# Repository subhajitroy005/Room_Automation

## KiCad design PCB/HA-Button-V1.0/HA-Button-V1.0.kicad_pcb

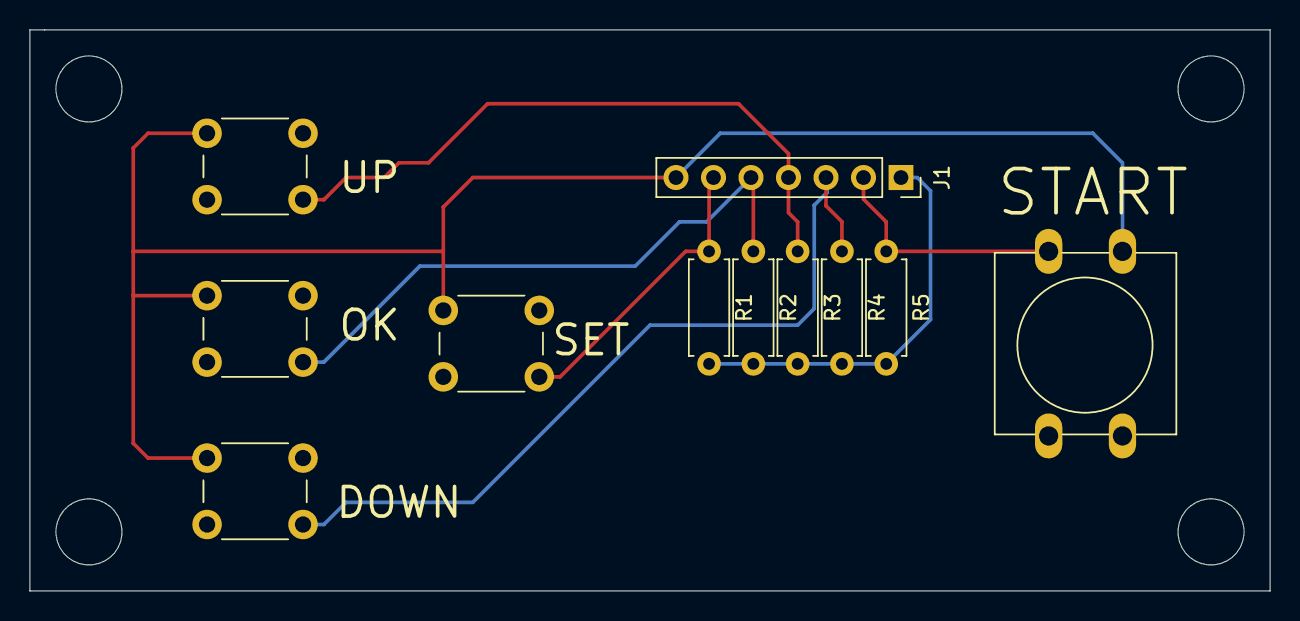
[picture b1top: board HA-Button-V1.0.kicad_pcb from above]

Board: 2 copper layers, 84.0 x 38.0 mm, 11 parts (0 on the bottom side), 7 nets.

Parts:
DOWN: DOWN; SW_PUSH_6mm
J1: MAIN_Board_Connecto; PinSocket_1x07_P2.54mm_Vertical
OK: OK; SW_PUSH_6mm
R1, R2, R3, R4: 1K; R_Axial_DIN0207_L6.3mm_D2.5mm_P7.62mm_Horizontal
R5: 1k; R_Axial_DIN0207_L6.3mm_D2.5mm_P7.62mm_Horizontal
SET: SETUP; SW_PUSH_6mm
START: Start; SW_PUSH-12mm
UP: UP; SW_PUSH_6mm

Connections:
5V-P: DOWN.1, J1.7, OK.1, SET.1, START.1, UP.1
DOWN_BTN: DOWN.2, J1.3, R4.1
GND: J1.1, R1.2, R2.2, R3.2, R4.2, R5.2
OK_BTN: J1.5, OK.2, R2.1
SET_BTN: J1.6, R1.1, SET.2
START_BTN: J1.2, R5.1, START.2
UP_BTN: J1.4, R3.1, UP.2

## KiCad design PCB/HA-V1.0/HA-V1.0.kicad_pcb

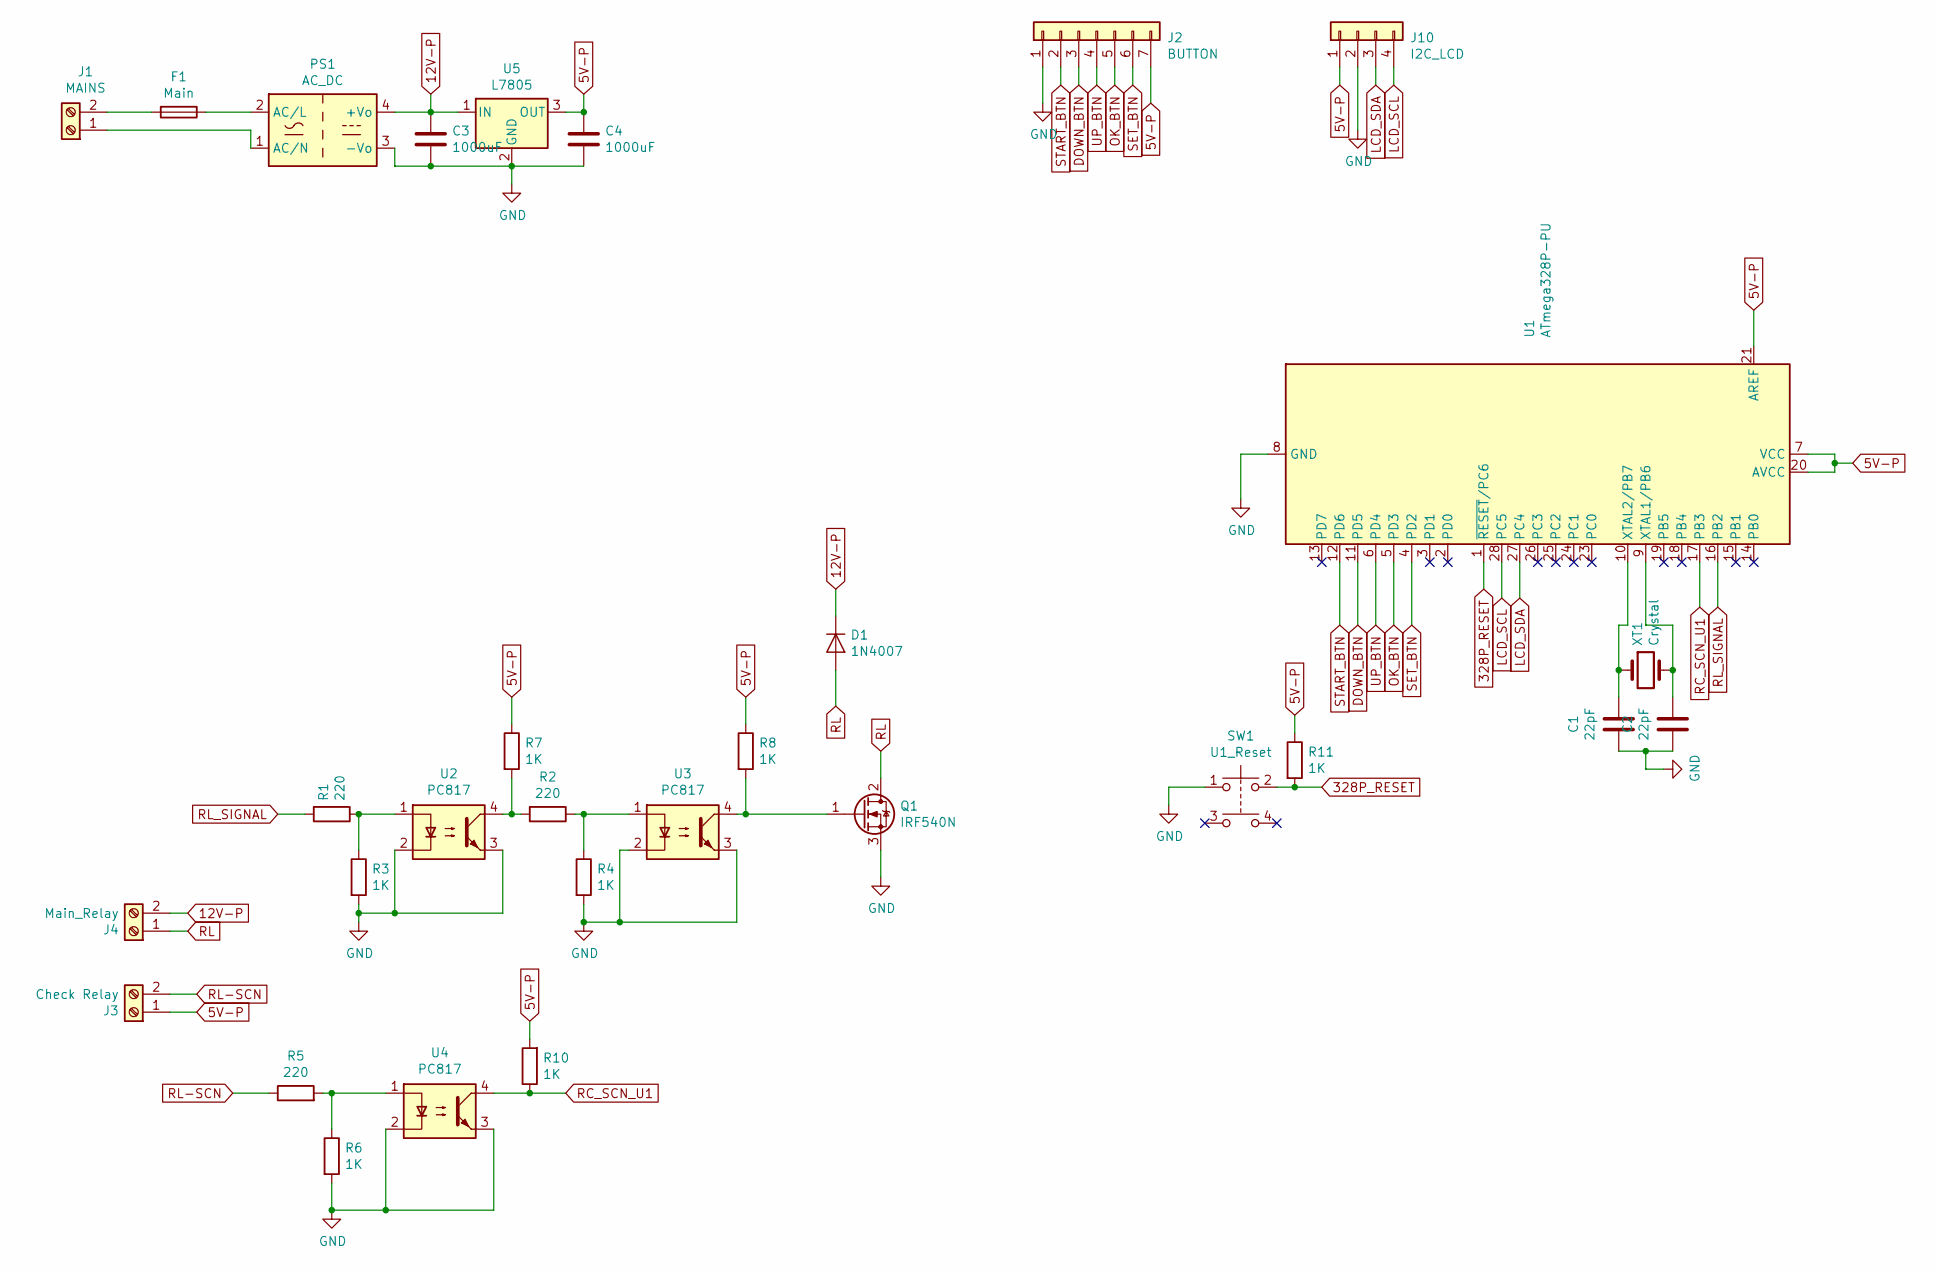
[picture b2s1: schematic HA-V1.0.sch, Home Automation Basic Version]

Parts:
C1, C2: 22pF; C_Disc_D3.0mm_W1.6mm_P2.50mm
C3, C4: 1000uF; C_Radial_D10.0mm_H16.0mm_P5.00mm
D1: 1N4007; D_DO-41_SOD81_P10.16mm_Horizontal
F1: Main; Fuse_SunFuse-6HP
J1: MAINS; PhoenixContact_MCV_1,5_2-G-5.08_1x02_P5.08mm_Vertical
J2: BUTTON; PinSocket_1x07_P2.54mm_Vertical
J3: Check Relay; TE_826576-2_1x02_P3.96mm_Vertical
J4: Main_Relay; TE_826576-2_1x02_P3.96mm_Vertical
J10: I2C_LCD; PinHeader_1x04_P2.54mm_Vertical; Digikey PN A101067-ND
PS1: AC_DC; Converter_ACDC_MeanWell_IRM-10-xx_THT
Q1: IRF540N; TO-220-3_Vertical
R1, R2, R5: 220; R_Axial_DIN0207_L6.3mm_D2.5mm_P7.62mm_Horizontal
R3, R4, R6, R7, R8, R10, R11: 1K; R_Axial_DIN0207_L6.3mm_D2.5mm_P7.62mm_Horizontal
SW1: U1_Reset; SW_PUSH_6mm_H4.3mm
U1: ATmega328P-PU; DIP-28_W7.62mm
U2, U3, U4: PC817; DIP-4_W7.62mm
U5: L7805; TO-220-3_Vertical
XT1: Crystal; Crystal_HC52-U_Vertical

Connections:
5V-P: C4.1, J2.7, J3.1, J10.1, R7.1, R8.1, R10.2, R11.1, U1.7 (VCC), U1.20 (AVCC), U1.21 (AREF), U5.3 (OUT); also elsewhere on the board
12V-P: C3.1, D1.1 (K), J4.2, PS1.4 (+Vo), U5.1 (IN); also elsewhere on the board
328P_RESET: R11.2, SW1.2, U1.1 (~RESET~/PC6)
DOWN_BTN: J2.3, U1.11 (PD5)
GND: C1.2, C2.2, C3.2, C4.2, J2.1, J10.2, PS1.3 (-Vo), Q1.3 (S), R3.2, R4.2, R6.2, SW1.1, U1.8 (GND), U1.22 (GND), U2.2, U2.3, U3.2, U3.3, U4.2, U4.3, U5.2 (GND)
LCD_SCL: J10.4, U1.28 (PC5)
LCD_SDA: J10.3, U1.27 (PC4)
unnamed: C1.1, U1.10 (XTAL2/PB7), XT1.1
unnamed: C2.1, U1.9 (XTAL1/PB6), XT1.2
unnamed: F1.1, PS1.2 (AC/L)
unnamed: F1.2, J1.2
unnamed: J1.1, PS1.1 (AC/N)
unnamed: Q1.1 (G), R8.2, U3.4
unnamed: R1.1, R3.1, U2.1
unnamed: R2.1, R4.1, U3.1
unnamed: R2.2, R7.2, U2.4
unnamed: R5.2, R6.1, U4.1
OK_BTN: J2.5, U1.5 (PD3)
RC_SCN_U1: R10.1, U1.17 (PB3), U4.4
RL: D1.2 (A), J4.1, Q1.2 (D); also elsewhere on the board
RL-SCN: J3.2, R5.1; also elsewhere on the board
RL_SIGNAL: R1.2, U1.16 (PB2)
SET_BTN: J2.6, U1.4 (PD2)
START_BTN: J2.2, U1.12 (PD6)
UP_BTN: J2.4, U1.6 (PD4)

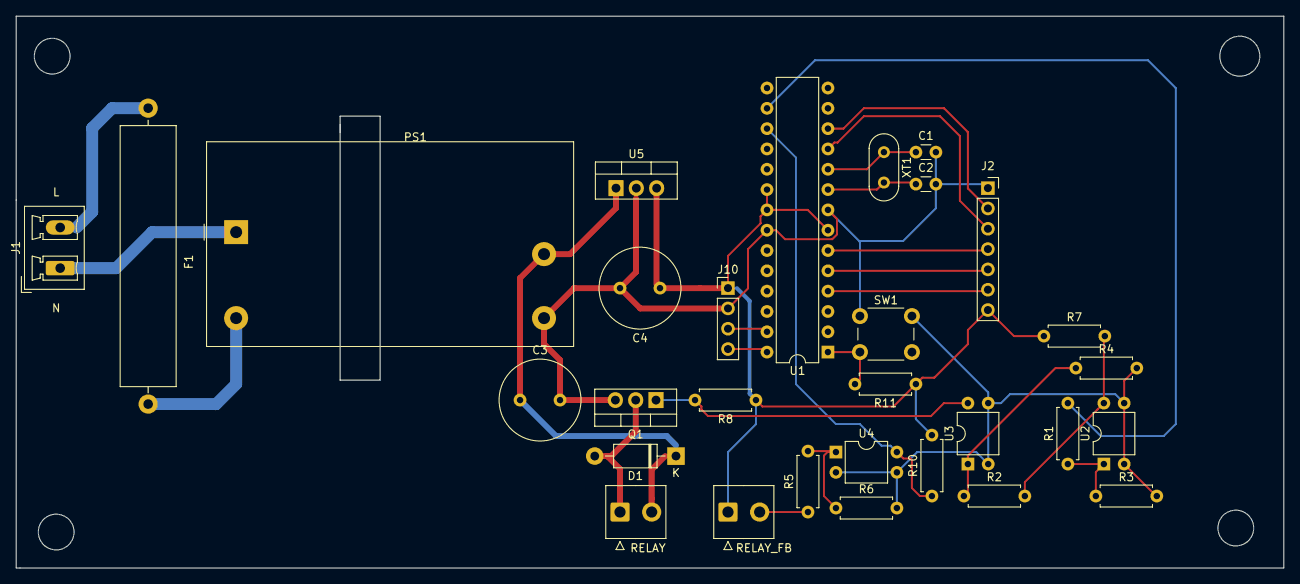
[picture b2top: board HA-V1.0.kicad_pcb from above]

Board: 2 copper layers, 158.5 x 69.0 mm, 30 parts (0 on the bottom side), 25 nets.

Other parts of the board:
RELAY: Main_Relay; TE_826576-2_1x02_P3.96mm_Vertical
RELAY_FB: Check Relay; TE_826576-2_1x02_P3.96mm_Vertical

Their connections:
5V-P: RELAY_FB.1; also elsewhere on the board
12V-P: RELAY.2; also elsewhere on the board
RL: RELAY.1; also elsewhere on the board
RL-SCN: RELAY_FB.2; also elsewhere on the board

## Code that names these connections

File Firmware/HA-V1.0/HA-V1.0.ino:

#include <Wire.h> 
#include <LiquidCrystal_I2C.h>
#include <EEPROM.h>

#define OK_BTN    5    // OK Button
#define UP_BTN    3    // UP Button
#define DOWN_BTN  2    // Down Button
#define SET_BTN   4    // SET Button
#define START_BTN 6    // Start and stop btn
#define RELAY 10
#define SCAN 11

#define ON HIGH
#define OFF LOW

struct _lcd_gui // Structure for controlling data on the gui
{
  unsigned char ok_btn = 0;
  unsigned char up_btn = 0;
  int up_btn_count = 0;
  unsigned char down_btn = 0;
  int down_btn_count =0;
  unsigned char set_btn = 0;
  unsigned char setup_status = 0;
}gui;

struct _motor
{
  unsigned char motor_run_status;
  unsigned char timer_value;
  unsigned char timer_counter;
  unsigned char relay_safe_status;
  unsigned char motor_start_index = 0;
  unsigned char start_btn_state = 0;
  unsigned char motor_start_pressed =0;
}motor;
 

int ok_buttonState;             // the current reading from the input pin
int last_ok_ButtonState = LOW;   // the previous reading from the input pin
unsigned long last_ok_DebounceTime = 0;  // the last time the output pin was toggled
int up_buttonState;             // the current reading from the input pin
int last_up_ButtonState = LOW;   // the previous reading from the input pin
unsigned long last_up_DebounceTime = 0;  // the last time the output pin was toggled
int down_buttonState;             // the current reading from the input pin
int last_down_ButtonState = LOW;   // the previous reading from the input pin
unsigned long last_down_DebounceTime = 0;  // the last time the output pin was toggled
int set_buttonState;             // the current reading from the input pin
int last_set_ButtonState = LOW;   // the previous reading from the input pin
unsigned long last_set_DebounceTime = 0;  // the last time the output pin was toggled
int start_buttonState;             // the current reading from the input pin
int last_start_ButtonState = LOW;   // the previous reading from the input pin
unsigned long last_start_DebounceTime = 0;  // the last time the output pin was toggled
unsigned long debounceDelay = 50;    // the debounce time; increase if the output flickers

unsigned long timer_1,time_index;
unsigned char motor_timer_start;
unsigned char run_forever = 1;
unsigned long millis_count;

LiquidCrystal_I2C lcd(0x27,16,2);  // set the LCD address to 0x27 for a 16 chars and 2 line display

void lcd_home(void);
void lcd_timer_setup(int up_btn_status);

void setup()
{
  // Variable initialization
   gui.ok_btn = 0;
   gui.up_btn = 0;
   gui.down_btn =0;
   gui.set_btn =0;
   gui.setup_status =0;

  pinMode(OK_BTN,INPUT);
  pinMode(UP_BTN,INPUT);
  pinMode(DOWN_BTN,INPUT);
  pinMode(SET_BTN,INPUT);
  pinMode(RELAY,OUTPUT);
  pinMode(SCAN,INPUT);
  
  lcd.init(); // Initialize the LCD            
  lcd.backlight(); // On the Back Light
  lcd.clear();
  lcd.setCursor(6,0);
  lcd.print("Hi");
  lcd.setCursor(2,1);
  lcd.print("Prabhat Roy");
  delay(2500);
  lcd.clear();
  lcd.setCursor(6,0);
  lcd.print("Hi");
  lcd.setCursor(2,1);
  lcd.print("Dipali Roy");
  delay(2500);
  // Initializing The Platform
  motor.start_btn_state = 0;
  motor.motor_run_status = 0;
  motor.motor_start_pressed = 0;
  motor.timer_value = EEPROM.read(0);
  motor_timer_start = 0;

  //Check Rleay
  if(digitalRead(SCAN))
    motor.relay_safe_status = 1;
  else
    motor.relay_safe_status = 0;
   
  lcd_home();
}

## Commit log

2020-07-13 Basic File Frormat
2020-07-14 Firmware- Scratch
2020-07-15 Arduino Code Scratch
2020-07-16 Code_release V1.0
2020-07-17 Firmware-RElay_Check Logic Invesion
2020-07-19 Final PCB Fabrication Done
2020-07-20 Partlist Updated
2022-10-23 :recycle: New base folder structure implemented.
